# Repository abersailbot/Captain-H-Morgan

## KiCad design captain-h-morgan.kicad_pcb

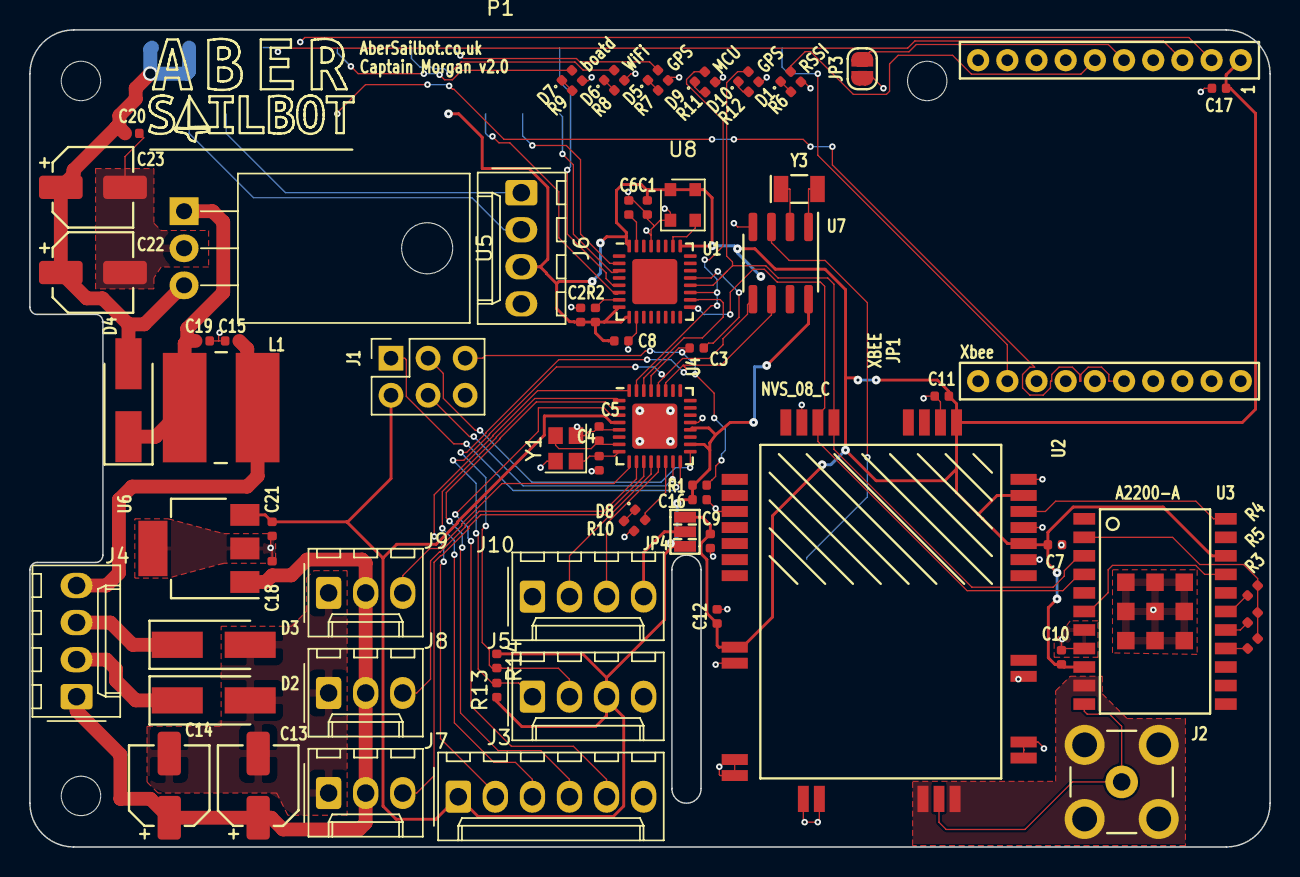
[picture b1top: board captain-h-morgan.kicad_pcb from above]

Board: 2 copper layers, 85.0 x 56.0 mm, 76 parts (1 on the bottom side), 69 nets.

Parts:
BT1: Battery_Cell; BatteryHolder_Keystone_3000_1x12mm
C1: 0.1uF; C_0402_1005Metric
C2, C7, C8, C10, C11, C12, C18, C20: 0.1uf; C_0402_1005Metric
C3: 100nf; C_0402_1005Metric
C4, C5: 22pf; C_0402_1005Metric
C6: 1uf; C_0402_1005Metric
C9: .1uf; C_0402_1005Metric
C13, C14, C22, C23: 47uf; CP_Elec_5x5.8
C15, C21: 10uf; C_0402_1005Metric
C16, C17: 3.3uf; C_0402_1005Metric
C19: 4.7uf; C_0402_1005Metric
D1, D5, D6, D7, D8, D9, D10: LED; LED_0402_1005Metric
D2, D3, D4: 40TE25; D_SMA_Handsoldering
J1: Conn_02x03_Odd_Even; PinSocket_2x03_P2.54mm_Vertical
J2: Conn_Coaxial_Power; SMB_Jack_Vertical
J3: Conn_01x06_Male; Molex_KK-254_AE-6410-06A_1x06_P2.54mm_Vertical
J4: Conn_01x04; Molex_KK-254_AE-6410-04A_1x04_P2.54mm_Vertical
J5, J6, J10: Conn_01x04_Male; Molex_KK-254_AE-6410-04A_1x04_P2.54mm_Vertical
J7, J8, J9: Conn_01x03_Male; Molex_KK-254_AE-6410-03A_1x03_P2.54mm_Vertical
JP1: XBEE
JP3: Jumper_2_Open; SolderJumper-2_P1.3mm_Open_RoundedPad1.0x1.5mm
JP4: Jumper_NC_Dual; 3p_Jumper
L1: 10uH; L_Wuerth_WE-PD2-Typ-L
MK1, MK2, MK3: M2.5; MountingHole_2.7mm_M2.5
P1: Conn_02x20_Odd_Even; Pi40SMD_REV
R1, R2, R4, R13, R14: 10k; R_0402_1005Metric
R3, R5: 2.2k; R_0402_1005Metric
R6, R7, R8, R9, R10, R11, R12: 33; R_0402_1005Metric
U1: MAX3109; QFN-32-1EP_5x5mm_P0.5mm_EP3.1x3.1mm
U2: NV08C-CSM; NV08C
U3: A2200-A; XCVR_A2200-A
U4: ATmega328PB-MU; QFN-32-1EP_5x5mm_P0.5mm_EP3.1x3.1mm
U5: R-78B-2.0; TO-220-3_Horizontal_TabDown
U6: LM2937xMP; SOT-223-3_TabPin2
U7: DS1307+; SOIC-8_3.9x4.9mm_P1.27mm
U8: DSC61XX; DSC61xx-CDFN4
Y1: 16Mhz; Crystal_SMD_2520-4Pin_2.5x2.0mm
Y3: 32.768khz; Crystal_SMD_MicroCrystal_CC7V-T1A-2Pin_3.2x1.5mm

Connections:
+3V3: C1.2, C2.2, C7.2, C8.2, C9.1, C10.2, C11.2, C12.1, C17.1, J6.3, JP1.1, JP4.1, P1.1, P1.17, R2.2, U1.8, U1.9, U1.25, U1.32, U2.8, U2.23, U2.26, U2.28, U3.9, U3.20, U8.1, U8.4
+5V: C20.1, C22.1, C23.1, D4.2, P1.2, P1.4, U5.3
/1v8: R3.2, R4.2, R5.2, U3.2
/Arduino: D8.2, U4.14
/Arduino_SCL: J5.2, R14.2, U4.27, U7.6
/Arduino_SDA: J5.1, R13.2, U4.28, U7.5
/Boat_D: D7.2, P1.12
/GPIO2(SDA1): J6.2, P1.3
/GPIO3(SCL1): J6.1, P1.5
/GPIO8(SPI0_CE_N): P1.24, U1.5
/GPIO9(SPI0_MISO): P1.21, U1.2
/GPIO10(SPI0_MOSI): P1.19, U1.6
/GPIO11(SPI0_SCK): P1.23, U1.3
/GPIO14(TXD0): JP1.3, P1.8
/GPIO15(RXD0): JP1.2, P1.10
/GPIO16: JP1.12, P1.36
/GPIO17(GEN0): JP1.16, P1.11
/GPIO23(GEN4): D6.2, P1.16
/GPIO24(GEN5): D5.2, P1.18
/GPS_ANT: J2.1, U2.15, U3.11
/GPS_ANT_GND: J2.2, U2.14, U2.16, U3.10
/GPS_RST: U2.25, U3.22
/GPS_RX: U1.17, U2.33, U3.4
/GPS_TX: D10.2, U1.20, U2.32, U3.3
/IRQ: R2.1, U1.7
/RC_IN_A: J3.2, U4.32
/RC_IN_B: J3.3, U4.1
/RC_IN_C: J3.4, U4.2
/RC_IN_D: J3.5, U4.3
/RC_V: C16.1, C21.1, J1.2, J3.1, J5.3, JP4.3, R1.2, R13.1, R14.1, U4.4, U4.18, U4.20, U6.3, U7.8
/SLF_ST: U3.6, U3.19
/Servo0: J7.3, U4.11
/Servo1: J8.3, U4.10
/Servo2: J9.3, U4.9
/Vcomp: C15.1, J4.4, L1.1
/Wind_Rx: J10.3, U4.13
/Wind_Tx-PluseIn: J10.2, U4.12
/arduino_rts: C3.1, U1.21
/arduino_rx: U1.18, U4.30
/arduino_tx: D9.2, U1.19, U4.31
/iscp_miso: J1.1, U4.16
/iscp_mosi: J1.4, U4.15
/iscp_rst: C3.2, J1.5, R1.1, U4.29
/iscp_sck: J1.3, U4.17
GND: BT1.2, C1.1, C2.1, C4.1, C5.1, C6.1, C7.1, C8.1, C9.2, C10.1, C11.1, C12.2, C13.2, C14.2, C15.2, C16.2, C17.2, C18.2, C19.2, C20.2, C21.2, C22.2, C23.2, D2.2, D3.2, J1.6, J3.6, J5.4, J6.4, J7.1, J8.1, J9.1, J10.1, JP1.10, JP3.1, P1.6, P1.9, P1.14, P1.20, P1.25, P1.30, P1.34, P1.39, R6.2, R7.2, R8.2, R9.2, R10.2, R11.2, R12.2, U1.10, U1.29, U2.3, U2.9, U2.10, U2.11, U2.12, U2.13, U2.17, U2.18, U2.19, U2.22, U2.24, U2.27, U2.29, U2.34, U3.7, U3.8, U3.23, U3.24, U3.25, U3.26, U3.27, U3.28, U3.29, U3.30, U3.31, U4.5, U4.21, U4.33, U5.2, U6.2, U7.4, U8.2, Y1.2, Y1.4
unnamed: BT1.1, U7.3
unnamed: C4.2, U4.8, Y1.1
unnamed: C5.2, U4.7, Y1.3
unnamed: C6.2, U1.31
unnamed: C19.1, D4.1, L1.2, U5.1
unnamed: D1.1, R6.1
unnamed: D1.2, JP1.6
unnamed: D2.1, J4.2
unnamed: D3.1, J4.3
unnamed: D5.1, R7.1
unnamed: D6.1, R8.1
unnamed: D7.1, R9.1
unnamed: D8.1, R10.1
unnamed: D9.1, R11.1
unnamed: D10.1, R12.1
unnamed: J10.4, JP4.2
unnamed: JP1.5, JP3.2
unnamed: R3.1, U3.15
unnamed: R4.1, U3.17
unnamed: R5.1, U3.16
unnamed: U1.26, U8.3
unnamed: U7.1, Y3.2
unnamed: U7.2, Y3.1
Vdrive: C13.1, C14.1, C18.1, J4.1, J7.2, J8.2, J9.2, U6.1

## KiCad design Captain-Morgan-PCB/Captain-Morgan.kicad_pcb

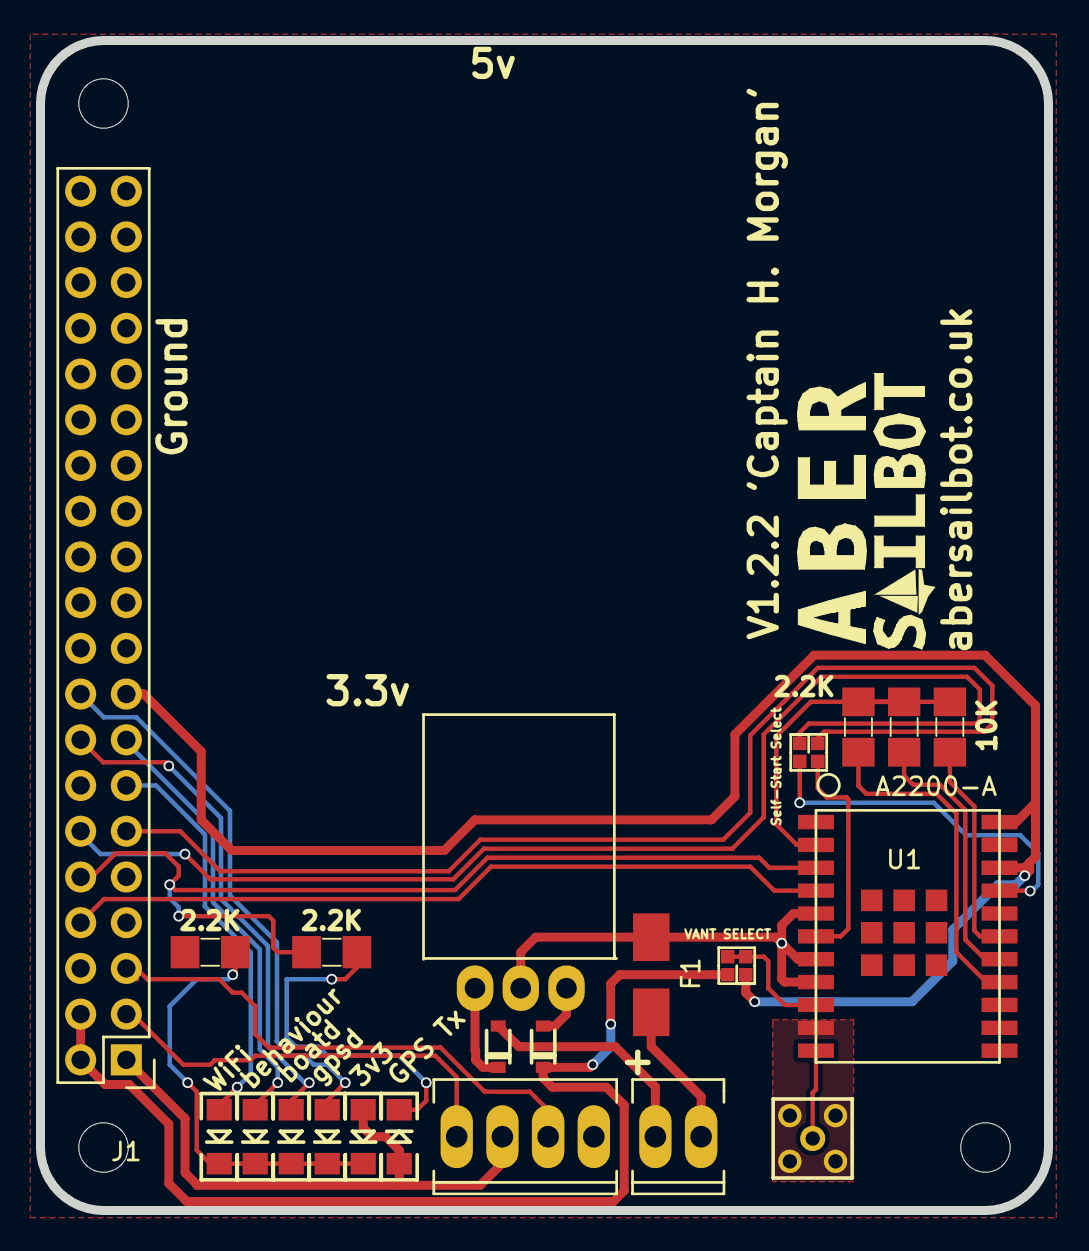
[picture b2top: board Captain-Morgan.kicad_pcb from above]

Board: 2 copper layers, 56.0 x 65.0 mm, 26 parts (0 on the bottom side), 28 nets.

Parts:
1111, 1112, 1121: RPi_Hat_Mounting_Hole
D1, D2: DIODE_SCHOTTKY; DIODE_SOD-323
F1: POLYFUSE; Fuse_SMD1206_HandSoldering
J1: RPi_GPIO; Pin_Header_Straight_2x20
J2: MMCX_H; MMCX_V
J3, J4: PINHEADER_2X2_SMD; 2-WAY-SMD-JUMPER
JP1: M02X02; Socket_MOLEX-KK-RM2-54mm_Lock_4pin_straight
LED1, LED2, LED3, LED4, LED5, LED6: LED; LED-1206
P1: BATT; Socket_MOLEX-KK-RM2-54mm_Lock_2pin_straight
R1: 10k; Resistor-1206
R2: 2.2K; Resistor-1206
R3, R4: 2.2k; Resistor-1206
R5: 2.2K; 1206
U1: A2200-A
U2: Racom R-78B5.0-1.5L; TO-220
svg2mod: G***; Sailbot_Logo

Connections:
+3V3: J1.1, J1.17, J4.3, JP1.3, LED5.A, LED6.A, U1.20, U1.22
+5V: D2.K, J1.2, J1.4, J4.1
GND: F1.1, J1.6, J1.9, J1.14, J1.20, J1.25, J1.30, J1.34, J1.39, JP1.1, R2.2, U1.5, U1.7, U1.8, U2.2
GPS_RX: J1.8, U1.4
GPS_TX: J1.10, R5.1, U1.3
unnamed: D1.A, P1.2
unnamed: D1.K, U2.1
unnamed: D2.A, U2.3
unnamed: F1.2, P1.1
unnamed: J1.3, JP1.4
unnamed: J1.5, JP1.2
unnamed: J2.1, U1.11
unnamed: J2.2, J2.3, J2.4, J2.5, U1.10
unnamed: J3.2, U1.6
unnamed: J3.4, U1.19
unnamed: J4.2, J4.4, U1.9
unnamed: LED1.K, LED2.K, LED3.K, LED4.K, LED6.K, R2.1
unnamed: LED5.K, R5.2
unnamed: R1.1, U1.17
unnamed: R3.1, U1.15
unnamed: R4.1, U1.16
ON_OFF: J1.11, J3.1
PI_LED_1: J1.13, LED1.A
PI_LED_2: J1.15, LED2.A
PI_LED_3: J1.16, LED3.A
PI_LED_4: J1.18, LED4.A
Vout-1v8: R1.2, R3.2, R4.2, U1.2
WAKEUP: J1.12, J3.3

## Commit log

2016-02-14 Rename Pi-Expansion -> pi-expansion
    Lower case names are nicer to deal with.
2016-02-15 added custom library for arduino board with only mounting holes, also added in the hole position for ardino, and refined pcb outline
2016-02-15 fixed board outline, moved gps
2016-02-16 did a full layout of the pcb, should be pretty much compleat, also fixed yet more issues librarys
2016-02-16 add copper fill for ground plane, and second mill revisions for prototyping
2016-05-16 Updated 3v3 and Gnd tabs on pi header on schmatic
2016-05-16 Adds reverse voltage protection for DC-DC converter allowing for safe operation of pi form UUSB connector
2016-05-16 Updated layout around gps, reconfigured for autowakeup and NMEA at 4800.
2016-05-16 minor tweaks, and rotated pi header, removed infill and traces
2016-05-19 Made minor tweaks to schematic layout, updated footprints and tweaked pcb layout
2016-05-19 First draft pcb layout, most tracks in place, footprints in near final positions
2016-05-19 Final Layout, Traces and footprints in place, added GPS_TX sensing circuit 3.3v powerled.
2016-05-20 updated power footprints, minor tweaks
2016-05-22 Silk screen update, nudged some footprints for better flow.
2016-05-22 Final Commit for V1.2 'Captain H.Morgan', all planes, solder masks, and components in final places.
2016-05-22 Documentation update, added notes to schematic.
2016-05-22 Documentation tweaks
2016-05-22 Updated GPS ground Pads
2016-05-23 updateded fab files with ground plane fix
2016-06-17 made minor mods to power supply including moving reverse protection diode from negitive side to positive side to reduce voltage drop.
2016-06-17 minor tweaks to in fill
2016-06-18 cleared out fabrication files as they should be generated fresh when needed, also simplified circuitry for the tx sense led
2016-06-18 Added current limiting resistor for GPS TX indicator, also fiddled with Copper fill
2016-06-18 updated led resistor placement so they no longer obstruct the legand on the silk screen
2016-06-30 Final version sent to fab, retraced GPS_TX to fix net issue between 2k2 resistor and pi header
2016-09-07 Added voltage select jumper to VANT.
2016-10-16 Added voltage select for GPS Vant between 5v and 3v3.
2016-11-21 Updated silkscreen typo.
2016-11-21 Nudged silkscreen for @tomgc96
2016-11-21 moved url to silkscreen and updated it for .co.uk address
2016-11-21 Moved led vias and traces to clear around silkscreen.
2016-11-21 de-capitalised gpsd
2016-12-02 Started cleaning up the repo, i am not even sure what these files do?
2016-12-02 Continued cleanup.
2016-12-02 Further cleanup.
2016-12-02 Added git ignore for several kicad tmp files
2016-12-02 Moved footprint files out of the repo to https://github.com/naturesyouth/Footprints.pretty
2016-12-04 re rendered board image and removed jpeg,
2016-12-04 Added Bom file for the Captain H Morgan PCB.
2017-06-19 Repo clean up, removing some uneeded files and and adding a .gitignore
2017-06-19 Further cleanup removing unneeded auto generated files.
2017-06-19 More file clean outs, and removed dependancy libarys in favour of switching to either kicad of project spesific ones.
2017-10-19 Repository cleanup and sorting, add folder for custom Pi-Firmware for working with more complex versions of Captain Morgan.
2017-10-19 Removed filled zone, arduino footprint and proto area.
2020-03-05 Replaces old captain morgan files with formally Captain Morgan Revengence.
